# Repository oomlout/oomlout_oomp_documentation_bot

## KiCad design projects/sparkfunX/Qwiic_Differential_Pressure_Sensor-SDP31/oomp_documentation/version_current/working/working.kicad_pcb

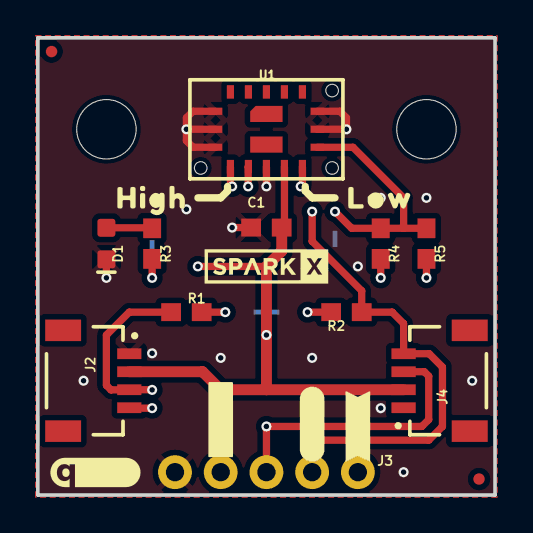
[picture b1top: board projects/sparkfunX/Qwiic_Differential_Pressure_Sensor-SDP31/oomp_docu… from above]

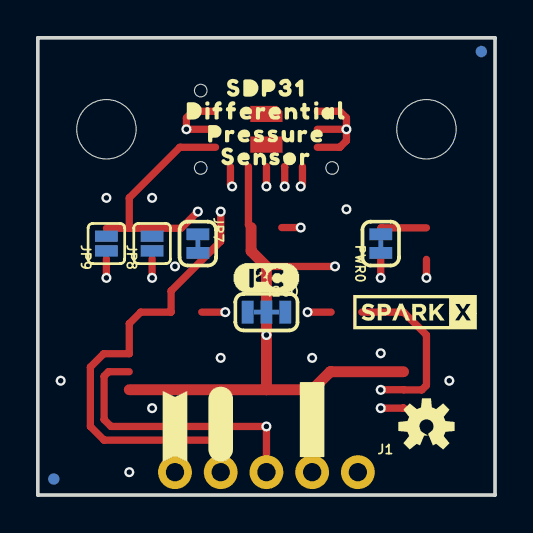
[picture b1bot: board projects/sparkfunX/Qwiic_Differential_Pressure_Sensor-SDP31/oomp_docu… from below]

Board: 4 copper layers, 25.4 x 25.4 mm, 52 parts (25 on the bottom side), 12 nets.

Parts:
C1: 0.1uF; 0603
D1: RED; LED-0603
FRAME1: FRAME-LETTER; CREATIVE_COMMONS
I2C0: JUMPER-SMT_3_2-NC_TRACE_SILK; SMT-JUMPER_3_2-NC_TRACE_SILK
J1: 1X04_NO_SILK
J2, J4: QWIIC_RIGHT_ANGLE; JST04_1MM_RA
J3: 1X01_NO_SILK
JP1, JP2, JP5, JP6: FIDUCIALUFIDUCIAL; FIDUCIAL-MICRO
JP3, JP4: STAND-OFF
JP7: JUMPER-SMT_2_NC_TRACE_SILK; SMT-JUMPER_2_NC_TRACE_SILK
JP8, JP9: JUMPER-SMT_2_NO_SILK; SMT-JUMPER_2_NO_SILK
LOGO1: SPECIAL_INSTRUCTIONS-ORDERING; ORDERING_INSTRUCTIONS
LOGO5: OSHW-LOGOS; OSHW-LOGO-S
PWR0: JUMPER-SMT_2_NC_TRACE_SILK; SMT-JUMPER_2_NC_TRACE_SILK
R1, R2: 4.7k; 0603
R3: 1k; 0603
R4: 1.20k; 0603
R5: 2.7k; 0603
U1: SDP31; SDP3X
U$1, U$33: #GND#0
U$2, U$34: #3#3V#0
U$3, U$35: #SDA#0
U$4, U$36: #SCL#0
U$5, U$6: ##INT##0
U$7: #0X21#0
U$8: #0X22#0
U$9: #0X23#0
U$10: DIFFERENTIAL0
U$11: PRESSURE0
U$12: SENSOR0
U$13: SDP310
U$14: #LED#0
U$15: I2C
U$16: QWIIC_5MM
U$17: HIGH0
U$18, U$20: SPARKX-LOGO3; SPARKX-SMALL
U$19: LOW0
U$21: #ADDRESS#0
U$32: #PWR#0

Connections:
3.3V: C1.1, I2C0.2, J1.2, J2.2, J4.2, PWR0.2, U1.7
ADDR: JP7.1, R4.1, R5.1, U1.9
GND: C1.2, D1.C, J1.1, J2.1, J4.1, JP7.2, JP8.2, JP9.2, U1.1, U1.2, U1.3, U1.6, U1.10, U1.11, U1.DIEPAD1, U1.DIEPAD2
unnamed: PWR0.1, R3.2
unnamed: I2C0.3, R1.2
unnamed: D1.A, R3.1
unnamed: I2C0.1, R2.2
unnamed: JP8.1, R4.2
unnamed: JP9.1, R5.2
SCL: J1.4, J2.4, J4.4, R2.1, U1.5
SDA: J1.3, J2.3, J4.3, R1.1, U1.8
~INT: J3.1, U1.4

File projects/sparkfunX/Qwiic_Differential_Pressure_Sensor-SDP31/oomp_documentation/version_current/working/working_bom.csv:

"Id";"Designator";"Footprint";"Quantity";"Designation";"Supplier and ref";
1;"U$32";"#PWR#0";1;"";;;
2;"JP2,JP6,JP5,JP1";"FIDUCIAL-MICRO";4;"FIDUCIALUFIDUCIAL";;;
3;"J3";"1X01_NO_SILK";1;"";;;
4;"U1";"SDP3X";1;"SDP31";;;
5;"U$17";"HIGH0";1;"";;;
6;"R1,R2";"0603";2;"4.7k";;;
7;"U$36,U$4";"#SCL#0";2;"";;;
8;"U$5,U$6";"##INT##0";2;"";;;
9;"U$16";"QWIIC_5MM";1;"";;;
10;"C1";"0603";1;"0.1uF";;;
11;"U$19";"LOW0";1;"";;;
12;"LOGO1";"ORDERING_INSTRUCTIONS";1;"SPECIAL_INSTRUCTIONS-ORDERING";;;
13;"J2,J4";"JST04_1MM_RA";2;"QWIIC_RIGHT_ANGLE";;;
14;"D1";"LED-0603";1;"RED";;;
15;"U$33,U$1";"#GND#0";2;"";;;
16;"R4";"0603";1;"1.20k";;;
17;"R5";"0603";1;"2.7k";;;
18;"FRAME1";"CREATIVE_COMMONS";1;"FRAME-LETTER";;;
19;"JP4,JP3";"STAND-OFF";2;"STAND-OFF";;;
20;"U$34,U$2";"#3#3V#0";2;"";;;
21;"U$20,U$18";"SPARKX-SMALL";2;"SPARKX-LOGO3";;;
22;"R3";"0603";1;"1k";;;
23;"U$35,U$3";"#SDA#0";2;"";;;
24;"U$21";"#ADDRESS#0";1;"";;;
25;"U$14";"#LED#0";1;"";;;
26;"U$13";"SDP310";1;"";;;
27;"JP9,JP8";"SMT-JUMPER_2_NO_SILK";2;"JUMPER-SMT_2_NO_SILK";;;
28;"U$11";"PRESSURE0";1;"";;;
29;"I2C0";"SMT-JUMPER_3_2-NC_TRACE_SILK";1;"JUMPER-SMT_3_2-NC_TRACE_SILK";;;
30;"J1";"1X04_NO_SILK";1;"";;;
31;"PWR0,JP7";"SMT-JUMPER_2_NC_TRACE_SILK";2;"JUMPER-SMT_2_NC_TRACE_SILK";;;
32;"U$7";"#0X21#0";1;"";;;
33;"U$9";"#0X23#0";1;"";;;
34;"U$10";"DIFFERENTIAL0";1;"";;;
35;"LOGO5";"OSHW-LOGO-S";1;"OSHW-LOGOS";;;
36;"U$8";"#0X22#0";1;"";;;
37;"U$12";"SENSOR0";1;"";;;
38;"U$15";"I2C";1;"";;;

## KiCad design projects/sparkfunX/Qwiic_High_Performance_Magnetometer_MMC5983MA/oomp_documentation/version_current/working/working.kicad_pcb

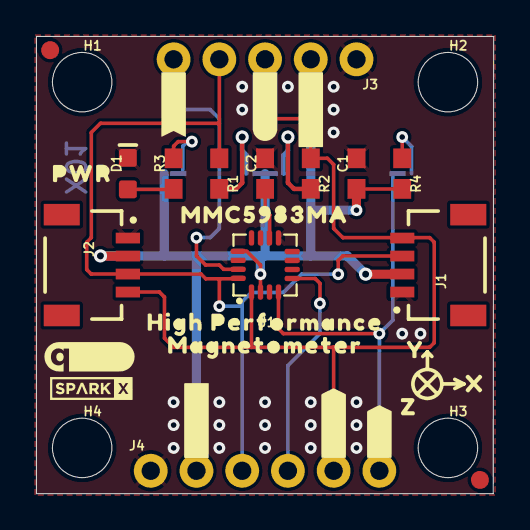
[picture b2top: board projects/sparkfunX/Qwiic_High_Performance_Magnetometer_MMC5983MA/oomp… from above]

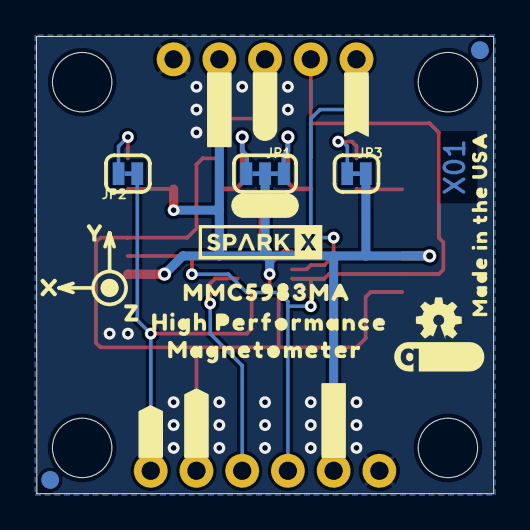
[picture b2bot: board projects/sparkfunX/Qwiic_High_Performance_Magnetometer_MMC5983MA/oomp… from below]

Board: 2 copper layers, 25.4 x 25.4 mm, 68 parts (29 on the bottom side), 13 nets.

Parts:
C1: 0.1uF; 0603
C2: 10uF; 0603
D1: RED; LED-0603
FD1, FD2, FD3, FD4: FIDUCIAL1X2; FIDUCIAL-1X2
FRAME1: FRAME-LETTERNO_PACKAGE; DUMMY
H1, H2, H3, H4: STAND-OFF
J1, J2: Qwiic; JST04_1MM_RA
J3: 1X05_NO_SILK
J4: 1X06_NO_SILK
JP1: JUMPER-SMT_3_2-NC_TRACE_SILK; SMT-JUMPER_3_2-NC_TRACE_SILK
JP2, JP3: JUMPER-SMT_2_NC_TRACE_SILK; SMT-JUMPER_2_NC_TRACE_SILK
LOGO1: OSHW-LOGOMINI; OSHW-LOGO-MINI
LOGO2, LOGO3: QWIIC_LOGO_5MM; QWIIC_5MM
R1, R2: 2.2k; 0603
R3: 1k; 0603
R4: 10k; 0603
U1: MMC5983MA_QFN16; LGA-16-3X3MM-4X4PINS
U$1, U$10: HIGH_PERFORMANCE11
U$2, U$35: #SCL#6
U$3, U$12, U$18, U$29: #3#3V#0
U$4, U$13, U$17, U$28: #GND#4
U$5, U$38: #SDA#5
U$6, U$31: #CIPO#11
U$7, U$16: #INT#7
U$8: PWR9
U$9, U$30: #COPI#12
U$11, U$24: MAGNETOMETER12
U$14, U$32: #SCK#13
U$15, U$33: ##CS##10
U$19, U$26: Y16
U$20, U$25: X15
U$21: #LED#8
U$22: #I2C#9
U$23: #SPI#9
U$27, U$39: Z17
U$34: MADE_IN_THE_USA20
U$36: SPARKX-LOGO2; SPARKX-TINY
U$37: SPARKX-LOGO3; SPARKX-SMALL
U$41, U$42: MMC5983MA0

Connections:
3.3V: C1.1, J1.2, J2.2, J3.2, J4.2, JP1.2, JP3.2, R4.2, U1.2, U1.13
CAP: C2.1, U1.10
CIPO: J4.4, U1.5
GND: C1.2, C2.2, D1.C, J1.1, J2.1, J3.1, J4.1, U1.9, U1.11
INT: J3.5, U1.15
unnamed: JP3.1, R3.2
unnamed: JP1.1, R2.2
unnamed: JP1.3, R1.2
unnamed: D1.A, R3.1
unnamed: JP2.2, R4.1
SCL/SCK: J1.4, J2.4, J3.3, J4.5, R2.1, U1.1
SDA/COPI: J1.3, J2.3, J3.4, J4.3, R1.1, U1.16
~CS: J4.6, JP2.1, U1.4

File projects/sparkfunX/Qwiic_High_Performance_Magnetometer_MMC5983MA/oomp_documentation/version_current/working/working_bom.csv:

"Id";"Designator";"Footprint";"Quantity";"Designation";"Supplier and ref";
1;"H3,H2,H4,H1";"STAND-OFF";4;"STAND-OFF";;;
2;"J2,J1";"JST04_1MM_RA";2;"Qwiic";;;
3;"U$5,U$38";"#SDA#5";2;"";;;
4;"FRAME1";"DUMMY";1;"FRAME-LETTERNO_PACKAGE";;;
5;"U$8";"PWR9";1;"";;;
6;"U$4,U$17,U$13,U$28";"#GND#4";4;"";;;
7;"U$3,U$18,U$29,U$12";"#3#3V#0";4;"";;;
8;"U$10,U$1";"HIGH_PERFORMANCE11";2;"";;;
9;"R2,R1";"0603";2;"2.2k";;;
10;"U$2,U$35";"#SCL#6";2;"";;;
11;"C2";"0603";1;"10uF";;;
12;"FD2,FD1,FD3,FD4";"FIDUCIAL-1X2";4;"FIDUCIAL1X2";;;
13;"U$41,U$42";"MMC5983MA0";2;"";;;
14;"U$20,U$25";"X15";2;"";;;
15;"U1";"LGA-16-3X3MM-4X4PINS";1;"MMC5983MA_QFN16";;;
16;"J4";"1X06_NO_SILK";1;"";;;
17;"D1";"LED-0603";1;"RED";;;
18;"U$19,U$26";"Y16";2;"";;;
19;"U$11,U$24";"MAGNETOMETER12";2;"";;;
20;"U$15,U$33";"##CS##10";2;"";;;
21;"U$9,U$30";"#COPI#12";2;"";;;
22;"LOGO3,LOGO2";"QWIIC_5MM";2;"QWIIC_LOGO_5MM";;;
23;"U$14,U$32";"#SCK#13";2;"";;;
24;"U$36";"SPARKX-TINY";1;"SPARKX-LOGO2";;;
25;"R4";"0603";1;"10k";;;
26;"R3";"0603";1;"1k";;;
27;"C1";"0603";1;"0.1uF";;;
28;"U$39,U$27";"Z17";2;"";;;
29;"U$7,U$16";"#INT#7";2;"";;;
30;"J3";"1X05_NO_SILK";1;"";;;
31;"U$6,U$31";"#CIPO#11";2;"";;;
32;"U$23";"#SPI#9";1;"";;;
33;"LOGO1";"OSHW-LOGO-MINI";1;"OSHW-LOGOMINI";;;
34;"JP3,JP2";"SMT-JUMPER_2_NC_TRACE_SILK";2;"JUMPER-SMT_2_NC_TRACE_SILK";;;
35;"U$34";"MADE_IN_THE_USA20";1;"";;;
36;"U$37";"SPARKX-SMALL";1;"SPARKX-LOGO3";;;
37;"U$21";"#LED#8";1;"";;;
38;"U$22";"#I2C#9";1;"";;;
39;"JP1";"SMT-JUMPER_3_2-NC_TRACE_SILK";1;"JUMPER-SMT_3_2-NC_TRACE_SILK";;;

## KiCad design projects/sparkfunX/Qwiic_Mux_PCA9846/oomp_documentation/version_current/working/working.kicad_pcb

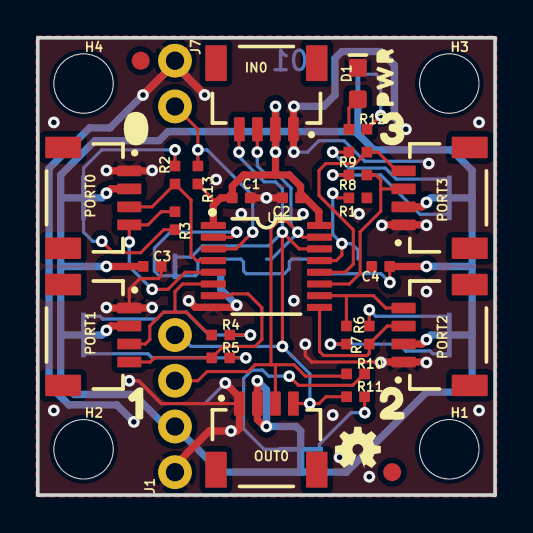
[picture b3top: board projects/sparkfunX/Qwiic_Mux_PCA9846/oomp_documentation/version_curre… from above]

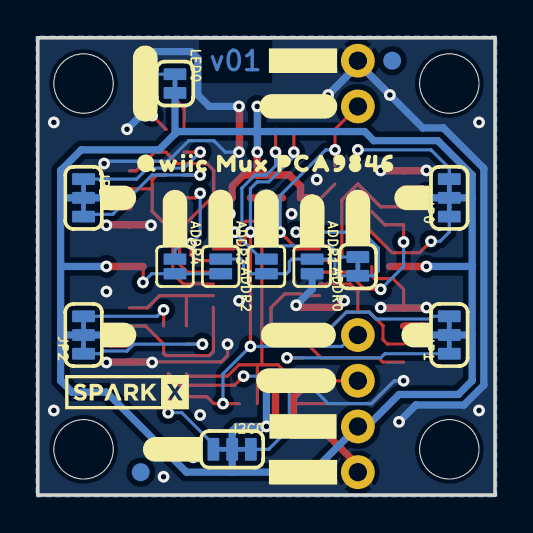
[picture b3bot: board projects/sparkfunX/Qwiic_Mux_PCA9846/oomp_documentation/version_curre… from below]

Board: 2 copper layers, 25.4 x 25.4 mm, 73 parts (32 on the bottom side), 27 nets.

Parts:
ADDR0: JUMPER-SMT_2_NC_TRACE_SILK; SMT-JUMPER_2_NC_TRACE_SILK
ADDR1, ADDR2, ADDR3, ADDR4: JUMPER-SMT_2_NO_SILK; SMT-JUMPER_2_NO_SILK
C1, C3, C4: 2.2uF; 0402-TIGHT
C2: 0.1uF; 0402-TIGHT
D1: RED; LED-0603
FD1, FD2, FD3, FD4: FIDUCIAL1X2; FIDUCIAL-1X2
FRAME1: FRAME-LETTER; CREATIVE_COMMONS
H1, H2, H3, H4: STAND-OFF
I2C0: JUMPER-SMT_3_2-NC_TRACE_SILK; SMT-JUMPER_3_2-NC_TRACE_SILK
IN0: QWIIC_RIGHT_ANGLE; JST04_1MM_RA
J1: 1X04_NO_SILK
J7: 1X02_NO_SILK
JP0, JP1, JP2, JP3: JUMPER-SMT_3_2-NC_TRACE_SILK; SMT-JUMPER_3_2-NC_TRACE_SILK
LED0: JUMPER-SMT_2_NC_TRACE_SILK; SMT-JUMPER_2_NC_TRACE_SILK
LOGO1: SPECIAL_INSTRUCTIONS-ORDERING; ORDERING_INSTRUCTIONS
LOGO4: OSHW-LOGOMINI; OSHW-LOGO-MINI
OUT0: QWIIC_RIGHT_ANGLE; JST04_1MM_RA
PORT0, PORT1, PORT2, PORT3: QWIIC_RIGHT_ANGLE; JST04_1MM_RA
R1, R13: 100k; 0402-TIGHT
R2, R3, R4, R5, R6, R7, R8, R9, R10, R11: 2.2k; 0402-TIGHT
R12: 1k; 0402-TIGHT
U1: PCA9846; SOT403-1
U$1: SPARKX-LOGO3; SPARKX-SMALL
U$2: PWR43214
U$3: 043215
U$4: 10
U$5: 211
U$6: 3212
U$7: ##RST##8
U$8: #0#9
U$9: #1#9
U$10: #2#9
U$11: #3#9
U$12: #3V3#7
U$13: #A0#0
U$14: #A1#1
U$15: #A2#2
U$16: #A3#3
U$17: #A4#4
U$18, U$19: #GND#7
U$21: #SCL#5
U$22: #SDA#6
U$23: #LED#0
U$24: QWIIC_MUX_PCA98461
U$25: #I�C#0

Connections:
3.3V: ADDR3.2, ADDR4.2, C1.1, C2.1, C3.1, C4.1, I2C0.2, IN0.2, J1.2, JP0.2, JP1.2, JP2.2, JP3.2, LED0.2, OUT0.2, PORT0.2, PORT1.2, PORT2.2, PORT3.2, R13.2, U1.1, U1.16
A0: ADDR0.1, ADDR1.1, ADDR2.1, ADDR3.1, U1.2
A1: ADDR4.1, R1.2, U1.13
GND: ADDR1.2, C1.2, C2.2, C3.2, C4.2, D1.C, IN0.1, J1.1, J7.1, OUT0.1, PORT0.1, PORT1.1, PORT2.1, PORT3.1, R1.1, U1.8
unnamed: JP0.3, R2.2
unnamed: JP0.1, R3.2
unnamed: JP1.3, R4.2
unnamed: JP1.1, R5.2
unnamed: JP2.3, R6.2
unnamed: JP2.1, R7.2
unnamed: JP3.3, R8.2
unnamed: JP3.1, R9.2
unnamed: I2C0.3, R10.2
unnamed: I2C0.1, R11.2
unnamed: LED0.1, R12.2
unnamed: D1.A, R12.1
SC0: PORT0.4, R3.1, U1.5
SC1: PORT1.4, R5.1, U1.7
SC2: PORT2.4, R7.1, U1.10
SC3: PORT3.4, R9.1, U1.12
SCL: ADDR0.2, IN0.4, J1.4, OUT0.4, R11.1, U1.14
SD0: PORT0.3, R2.1, U1.4
SD1: PORT1.3, R4.1, U1.6
SD2: PORT2.3, R6.1, U1.9
SD3: PORT3.3, R8.1, U1.11
SDA: ADDR2.2, IN0.3, J1.3, OUT0.3, R10.1, U1.15
~RESET: J7.2, R13.1, U1.3

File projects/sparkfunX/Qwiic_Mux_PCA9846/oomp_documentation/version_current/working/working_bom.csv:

"Id";"Designator";"Footprint";"Quantity";"Designation";"Supplier and ref";
1;"U$4";"10";1;"";;;
2;"R10,R7,R9,R5,R11,R8,R4,R2,R3,R6";"0402-TIGHT";10;"2.2k";;;
3;"U1";"SOT403-1";1;"PCA9846";;;
4;"FRAME1";"CREATIVE_COMMONS";1;"FRAME-LETTER";;;
5;"PORT1,PORT0,PORT3,OUT0,PORT2,IN0";"JST04_1MM_RA";6;"QWIIC_RIGHT_ANGLE";;;
6;"H3,H4,H2,H1";"STAND-OFF";4;"STAND-OFF";;;
7;"U$3";"043215";1;"";;;
8;"D1";"LED-0603";1;"RED";;;
9;"C4,C1,C3";"0402-TIGHT";3;"2.2uF";;;
10;"R1,R13";"0402-TIGHT";2;"100k";;;
11;"C2";"0402-TIGHT";1;"0.1uF";;;
12;"J7";"1X02_NO_SILK";1;"";;;
13;"LOGO1";"ORDERING_INSTRUCTIONS";1;"SPECIAL_INSTRUCTIONS-ORDERING";;;
14;"J1";"1X04_NO_SILK";1;"";;;
15;"R12";"0402-TIGHT";1;"1k";;;
16;"FD2,FD1,FD4,FD3";"FIDUCIAL-1X2";4;"FIDUCIAL1X2";;;
17;"U$2";"PWR43214";1;"";;;
18;"LOGO4";"OSHW-LOGO-MINI";1;"OSHW-LOGOMINI";;;
19;"U$6";"3212";1;"";;;
20;"U$5";"211";1;"";;;
21;"U$17";"#A4#4";1;"";;;
22;"U$14";"#A1#1";1;"";;;
23;"U$11";"#3#9";1;"";;;
24;"U$16";"#A3#3";1;"";;;
25;"JP2,I2C0,JP0,JP1,JP3";"SMT-JUMPER_3_2-NC_TRACE_SILK";5;"JUMPER-SMT_3_2-NC_TRACE_SILK";;;
26;"U$1";"SPARKX-SMALL";1;"SPARKX-LOGO3";;;
27;"U$9";"#1#9";1;"";;;
28;"U$10";"#2#9";1;"";;;
29;"ADDR3,ADDR4,ADDR2,ADDR1";"SMT-JUMPER_2_NO_SILK";4;"JUMPER-SMT_2_NO_SILK";;;
30;"U$12";"#3V3#7";1;"";;;
31;"ADDR0,LED0";"SMT-JUMPER_2_NC_TRACE_SILK";2;"JUMPER-SMT_2_NC_TRACE_SILK";;;
32;"U$18,U$19";"#GND#7";2;"";;;
33;"U$24";"QWIIC_MUX_PCA98461";1;"";;;
34;"U$23";"#LED#0";1;"";;;
35;"U$22";"#SDA#6";1;"";;;
36;"U$21";"#SCL#5";1;"";;;
37;"U$7";"##RST##8";1;"";;;
38;"U$13";"#A0#0";1;"";;;
39;"U$8";"#0#9";1;"";;;
40;"U$25";"#I�C#0";1;"";;;
41;"U$15";"#A2#2";1;"";;;

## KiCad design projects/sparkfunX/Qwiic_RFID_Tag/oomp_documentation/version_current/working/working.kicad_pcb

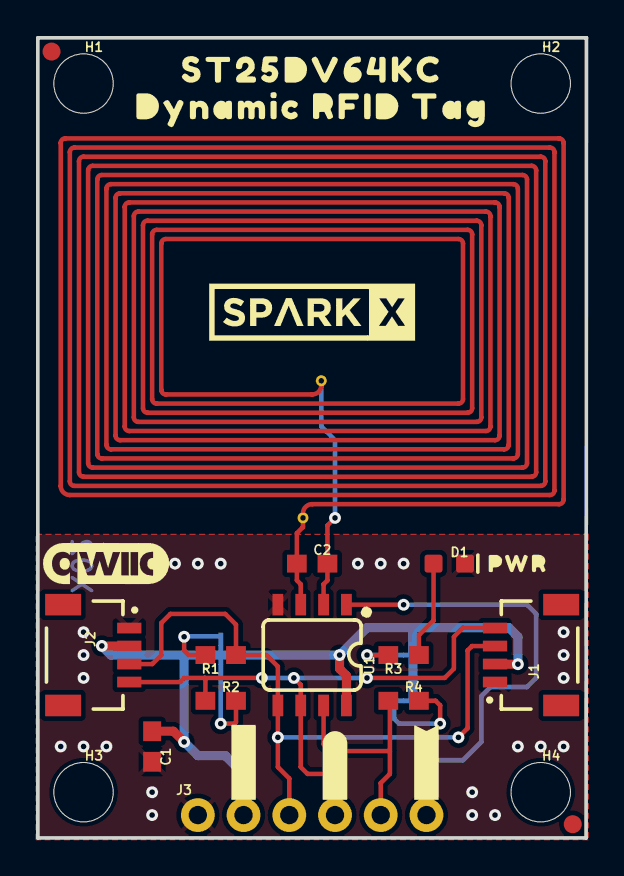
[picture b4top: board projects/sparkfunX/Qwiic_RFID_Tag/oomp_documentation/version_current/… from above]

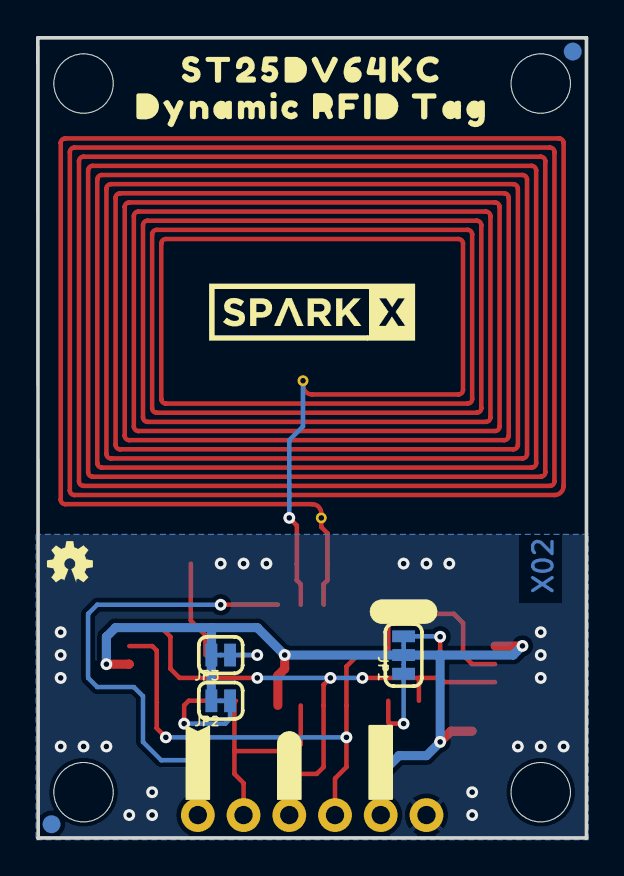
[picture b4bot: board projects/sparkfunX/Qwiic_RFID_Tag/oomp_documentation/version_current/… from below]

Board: 2 copper layers, 30.5 x 44.5 mm, 48 parts (18 on the bottom side), 13 nets.

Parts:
C1: 0.1uF; 0603
C2: 4.7pF; 0603
D1: RED; LED-0603
FD1, FD2, FD3, FD4: FIDUCIAL1X2; FIDUCIAL-1X2
FRAME1: FRAME-LETTERNO_PACKAGE; DUMMY
H1, H2, H3, H4: STAND-OFF
J1, J2: Qwiic; JST04_1MM_RA
J3: 1X06_NO_SILK
JP1: JUMPER-SMT_3_2-NC_TRACE_SILK; SMT-JUMPER_3_2-NC_TRACE_SILK
JP2, JP3: JUMPER-SMT_2_NC_TRACE_SILK; SMT-JUMPER_2_NC_TRACE_SILK
L1: PCB_4UH_INDUCTOR
LOGO1: OSHW-LOGOMINI; OSHW-LOGO-MINI
LOGO3: QWIIC_LOGO_7MM; QWIIC_7MM
R1, R2: 2.2k; 0603
R3: 1k; 0603
R4: 10k; 0603
U1: ST25DV64KC; SO08
U$1, U$2: SPARKX-LOGO5; SPARKX-LARGE
U$3, U$19: #3#3V#0
U$4, U$18: #GND#4
U$5, U$20: #SDA#5
U$6, U$21: #SCL#6
U$7, U$22: ##GPO##8
U$8, U$23: #VEH#7
U$9: PWR11
U$10, U$11: DYNAMIC_RFID_TAG0
U$13, U$24: ST25DV64KC5984
U$15: #I2C#11
U$16: ##GPO##9
U$17: #LED#10

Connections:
3.3V: C1.1, J1.2, J2.2, J3.2, JP1.2, JP2.2, JP3.2, U1.8
AC0: C2.2, L1.IN1, U1.2
AC1: C2.1, L1.IN2, U1.3
GND: C1.2, D1.C, J1.1, J2.1, J3.1, U1.4
unnamed: JP3.1, R3.2
unnamed: JP1.3, R1.2
unnamed: JP1.1, R2.2
unnamed: D1.A, R3.1
unnamed: JP2.1, R4.2
SCL: J1.4, J2.4, J3.4, R2.1, U1.6
SDA: J1.3, J2.3, J3.3, R1.1, U1.5
VEH: J3.6, U1.1
~GPO: J3.5, R4.1, U1.7

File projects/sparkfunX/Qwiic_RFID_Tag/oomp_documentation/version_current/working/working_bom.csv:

"Id";"Designator";"Footprint";"Quantity";"Designation";"Supplier and ref";
1;"FD4,FD2,FD3,FD1";"FIDUCIAL-1X2";4;"FIDUCIAL1X2";;;
2;"R2,R1";"0603";2;"2.2k";;;
3;"FRAME1";"DUMMY";1;"FRAME-LETTERNO_PACKAGE";;;
4;"C1";"0603";1;"0.1uF";;;
5;"R3";"0603";1;"1k";;;
6;"U$7,U$22";"##GPO##8";2;"";;;
7;"H4,H2,H3,H1";"STAND-OFF";4;"STAND-OFF";;;
8;"U1";"SO08";1;"ST25DV64KC";;;
9;"U$9";"PWR11";1;"";;;
10;"U$10,U$11";"DYNAMIC_RFID_TAG0";2;"";;;
11;"U$13,U$24";"ST25DV64KC5984";2;"";;;
12;"D1";"LED-0603";1;"RED";;;
13;"R4";"0603";1;"10k";;;
14;"U$4,U$18";"#GND#4";2;"";;;
15;"U$5,U$20";"#SDA#5";2;"";;;
16;"U$8,U$23";"#VEH#7";2;"";;;
17;"LOGO3";"QWIIC_7MM";1;"QWIIC_LOGO_7MM";;;
18;"J3";"1X06_NO_SILK";1;"";;;
19;"J2,J1";"JST04_1MM_RA";2;"Qwiic";;;
20;"U$6,U$21";"#SCL#6";2;"";;;
21;"U$3,U$19";"#3#3V#0";2;"";;;
22;"U$1,U$2";"SPARKX-LARGE";2;"SPARKX-LOGO5";;;
23;"C2";"0603";1;"4.7pF";;;
24;"L1";"PCB_4UH_INDUCTOR";1;"PCB_4UH_INDUCTOR";;;
25;"U$16";"##GPO##9";1;"";;;
26;"LOGO1";"OSHW-LOGO-MINI";1;"OSHW-LOGOMINI";;;
27;"U$15";"#I2C#11";1;"";;;
28;"U$17";"#LED#10";1;"";;;
29;"JP1";"SMT-JUMPER_3_2-NC_TRACE_SILK";1;"JUMPER-SMT_3_2-NC_TRACE_SILK";;;
30;"JP3,JP2";"SMT-JUMPER_2_NC_TRACE_SILK";2;"JUMPER-SMT_2_NC_TRACE_SILK";;;

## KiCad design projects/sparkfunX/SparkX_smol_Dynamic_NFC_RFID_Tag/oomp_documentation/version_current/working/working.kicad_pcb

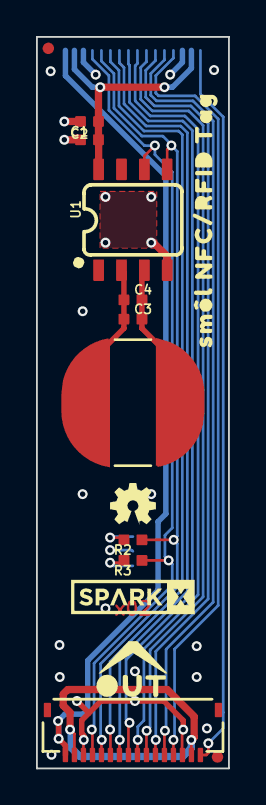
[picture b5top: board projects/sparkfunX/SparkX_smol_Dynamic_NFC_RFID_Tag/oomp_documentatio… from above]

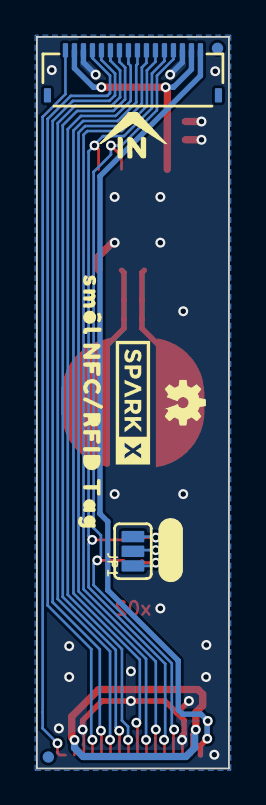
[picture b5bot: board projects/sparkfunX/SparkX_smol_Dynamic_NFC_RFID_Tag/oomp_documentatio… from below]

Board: 4 copper layers, 10.7 x 40.6 mm, 28 parts (10 on the bottom side), 18 nets.

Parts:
ANT0: 4.7μH; W3102
C1: 0.1uF; 0402-TIGHT
C2: 2.2uF; 0402-TIGHT
C3: DNP; 0402-TIGHT_NO_CREAM
C4: 0.5pF; 0402-TIGHT
FD1, FD2, FD3, FD4: FIDUCIALUFIDUCIAL; FIDUCIAL-MICRO
FRAME1: FRAME-LEDGER; CREATIVE_COMMONS
IN0: FPC_16_0.5MM
JP1: JUMPER-SMT_3_NO_SILK; SMT-JUMPER_3_NO_SILK
LOGO1: SPECIAL_INSTRUCTIONS-ORDERING; ORDERING_INSTRUCTIONS
LOGO2, LOGO3: OSHW-LOGOMINI; OSHW-LOGO-MINI
OUT0: FPC_16_0.5MM
R2, R3: 4.7k; 0402-TIGHT
U1: ST25DV64KC; SO08
U$1, U$20: SPARKX-LOGO3; SPARKX-SMALL
U$2, U$4: SM�L_NFC#RFID_TAG0
U$3, U$9: SMOL_LOGOSMALL; SMOL_SMALL
U$5: #I�C#0
U$8: IN0
U$17: OUT0

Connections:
3.3V: C1.1, C2.1, IN0.2, IN0.15, JP1.2, OUT0.2, OUT0.15, U1.8
CIPO: IN0.6, OUT0.6
COPI: IN0.5, OUT0.5
CS0: IN0.7, OUT0.7
CS1: IN0.8, OUT0.8
CS2: IN0.9, OUT0.9
GND: C1.2, C2.2, IN0.3, IN0.14, OUT0.3, OUT0.14, U1.4
GPIO0: IN0.10, OUT0.10
GPIO1: IN0.11, OUT0.11
unnamed: ANT0.2, C3.2, C4.2, U1.3
unnamed: ANT0.1, C3.1, C4.1, U1.2
unnamed: JP1.3, R2.2
unnamed: JP1.1, R3.2
PROC_PWR_EN: IN0.1, OUT0.1
SCL: IN0.13, OUT0.13, R3.1, U1.6
SCLK: IN0.4, OUT0.4
SDA: IN0.12, OUT0.12, R2.1, U1.5
V_USB: IN0.16, OUT0.16

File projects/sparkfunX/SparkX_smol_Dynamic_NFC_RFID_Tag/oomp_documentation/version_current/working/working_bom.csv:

"Id";"Designator";"Footprint";"Quantity";"Designation";"Supplier and ref";
1;"FD3,FD1,FD2,FD4";"FIDUCIAL-MICRO";4;"FIDUCIALUFIDUCIAL";;;
2;"R2,R3";"0402-TIGHT";2;"4.7k";;;
3;"C3";"0402-TIGHT_NO_CREAM";1;"DNP";;;
4;"U$3,U$9";"SMOL_SMALL";2;"SMOL_LOGOSMALL";;;
5;"FRAME1";"CREATIVE_COMMONS";1;"FRAME-LEDGER";;;
6;"OUT0,IN0";"FPC_16_0.5MM";2;"";;;
7;"U$17";"OUT0";1;"";;;
8;"LOGO1";"ORDERING_INSTRUCTIONS";1;"SPECIAL_INSTRUCTIONS-ORDERING";;;
9;"C2";"0402-TIGHT";1;"2.2uF";;;
10;"LOGO2,LOGO3";"OSHW-LOGO-MINI";2;"OSHW-LOGOMINI";;;
11;"C4";"0402-TIGHT";1;"0.5pF";;;
12;"U$1,U$20";"SPARKX-SMALL";2;"SPARKX-LOGO3";;;
13;"U1";"SO08";1;"ST25DV64KC";;;
14;"C1";"0402-TIGHT";1;"0.1uF";;;
15;"U$2,U$4";"SM�L_NFC#RFID_TAG0";2;"";;;
16;"ANT0";"W3102";1;"4.7μH";;;
17;"U$8";"IN0";1;"";;;
18;"U$5";"#I�C#0";1;"";;;
19;"JP1";"SMT-JUMPER_3_NO_SILK";1;"JUMPER-SMT_3_NO_SILK";;;

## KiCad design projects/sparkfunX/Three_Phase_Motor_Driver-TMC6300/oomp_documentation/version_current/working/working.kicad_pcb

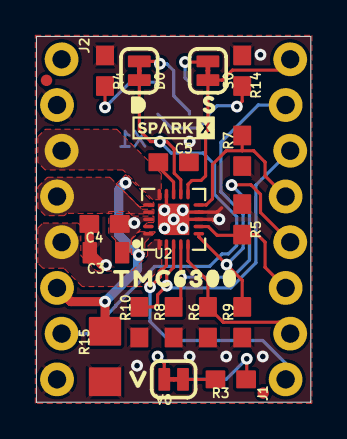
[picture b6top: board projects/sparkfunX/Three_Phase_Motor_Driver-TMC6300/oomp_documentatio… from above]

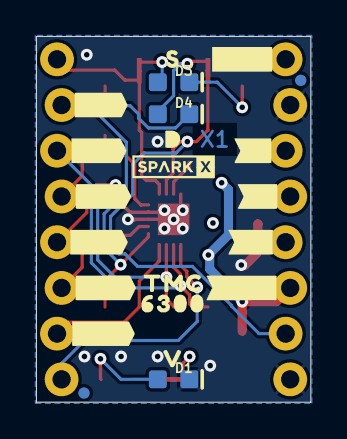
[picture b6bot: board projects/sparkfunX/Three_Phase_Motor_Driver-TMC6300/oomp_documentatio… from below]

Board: 4 copper layers, 15.2 x 20.3 mm, 56 parts (28 on the bottom side), 22 nets.

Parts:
C3: 10uF; 0805
C4, C5: 0.1uF; 0603
D0: JUMPER-SMT_2_NC_TRACE_SILK; SMT-JUMPER_2_NC_TRACE_SILK
D1: RED; LED-0603
D3: BLUE; LED-0603
D4: GREEN; LED-0603
FD1, FD2, FD3, FD4: FIDUCIALUFIDUCIAL; FIDUCIAL-MICRO
FRAME1: FRAME-LETTER; CREATIVE_COMMONS
J1, J2: 1X08_LOCK_NO_SILK
LOGO1: OSHW-LOGONO_SILK; DUMMY
LOGO2: SPECIAL_INSTRUCTIONS-ORDERING; ORDERING_INSTRUCTIONS
R3: 1k; 0603
R4, R14: 330; 0603
R5, R6, R7, R8, R9, R10: 100k; 0603
R15: 0.12; 1206
S0: JUMPER-SMT_2_NC_TRACE_SILK; SMT-JUMPER_2_NC_TRACE_SILK
U2: TMC6300; QFN-20
U$1, U$28: #GND#1
U$2: #SEN#0
U$3: #DIAG#0
U$9: #U#6
U$12: #VCP#0
U$13: #VIO#1
U$15: 63001
U$16, U$18: D0
U$17: TMC63000
U$19, U$27: S1
U$20, U$26: V2
U$21: #UH#5
U$22: #UL#4
U$23: TMC0
U$24: #VIN#0
U$25: #V#7
U$30: #VH#2
U$31: #VL#3
U$32: #W#8
U$33: #WH#1
U$34: #WL#0
U$36, U$37: SPARKX-LOGO2; SPARKX-TINY
V0: JUMPER-SMT_2_NC_TRACE_SILK; SMT-JUMPER_2_NC_TRACE_SILK

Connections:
DIAG: D0.2, J2.7, U2.12
GND: C3.2, C4.2, C5.2, D1.C, J2.2, J2.8, R4.1, R5.1, R6.1, R7.1, R8.1, R9.1, R10.1, R14.1, R15.1, U2.8, U2.9, U2.14, U2.PAD
unnamed: R3.2, V0.1
unnamed: D1.A, R3.1
unnamed: D3.A, S0.1
unnamed: C5.1, U2.13
unnamed: D0.1, D4.A
unnamed: D3.C, R4.2
unnamed: D4.C, R14.2
SENSE: J2.6, R15.2, U2.16, U2.20
U: J2.3, U2.15
UH: J1.6, R10.2, U2.3
UL: J1.7, R9.2, U2.6
V: J2.4, U2.17
VCP: J1.1, U2.2
VH: J1.4, R8.2, U2.4
VIN: C3.1, C4.1, J2.1, U2.18, V0.2
VIO/~STDBY: J1.8, S0.2, U2.11
VL: J1.5, R7.2, U2.10
W: J2.5, U2.1
WH: J1.2, R6.2, U2.5
WL: J1.3, R5.2, U2.7

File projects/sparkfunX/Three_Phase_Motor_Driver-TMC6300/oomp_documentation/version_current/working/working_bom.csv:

"Id";"Designator";"Footprint";"Quantity";"Designation";"Supplier and ref";
1;"R9,R10,R8,R7,R6,R5";"0603";6;"100k";;;
2;"U$16,U$18";"D0";2;"";;;
3;"V0,D0,S0";"SMT-JUMPER_2_NC_TRACE_SILK";3;"JUMPER-SMT_2_NC_TRACE_SILK";;;
4;"J1,J2";"1X08_LOCK_NO_SILK";2;"";;;
5;"U$26,U$20";"V2";2;"";;;
6;"R3";"0603";1;"1k";;;
7;"R14,R4";"0603";2;"330";;;
8;"U$17";"TMC63000";1;"";;;
9;"R15";"1206";1;"0.12";;;
10;"C4,C5";"0603";2;"0.1uF";;;
11;"FRAME1";"CREATIVE_COMMONS";1;"FRAME-LETTER";;;
12;"U$27,U$19";"S1";2;"";;;
13;"LOGO2";"ORDERING_INSTRUCTIONS";1;"SPECIAL_INSTRUCTIONS-ORDERING";;;
14;"C3";"0805";1;"10uF";;;
15;"FD2,FD1,FD4,FD3";"FIDUCIAL-MICRO";4;"FIDUCIALUFIDUCIAL";;;
16;"U$36,U$37";"SPARKX-TINY";2;"SPARKX-LOGO2";;;
17;"U2";"QFN-20";1;"TMC6300";;;
18;"U$25";"#V#7";1;"";;;
19;"D4";"LED-0603";1;"GREEN";;;
20;"U$31";"#VL#3";1;"";;;
21;"U$32";"#W#8";1;"";;;
22;"U$9";"#U#6";1;"";;;
23;"D1";"LED-0603";1;"RED";;;
24;"U$22";"#UL#4";1;"";;;
25;"U$33";"#WH#1";1;"";;;
26;"U$1,U$28";"#GND#1";2;"";;;
27;"U$13";"#VIO#1";1;"";;;
28;"U$15";"63001";1;"";;;
29;"U$30";"#VH#2";1;"";;;
30;"LOGO1";"DUMMY";1;"OSHW-LOGONO_SILK";;;
31;"U$12";"#VCP#0";1;"";;;
32;"U$21";"#UH#5";1;"";;;
33;"U$23";"TMC0";1;"";;;
34;"U$34";"#WL#0";1;"";;;
35;"U$24";"#VIN#0";1;"";;;
36;"U$2";"#SEN#0";1;"";;;
37;"U$3";"#DIAG#0";1;"";;;
38;"D3";"LED-0603";1;"BLUE";;;

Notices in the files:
parts and their libraries:
https://creativecommons.org/licenses/by-sa/4.0
Released under the Creative Commons Attribution Share-Alike 4.0 License
